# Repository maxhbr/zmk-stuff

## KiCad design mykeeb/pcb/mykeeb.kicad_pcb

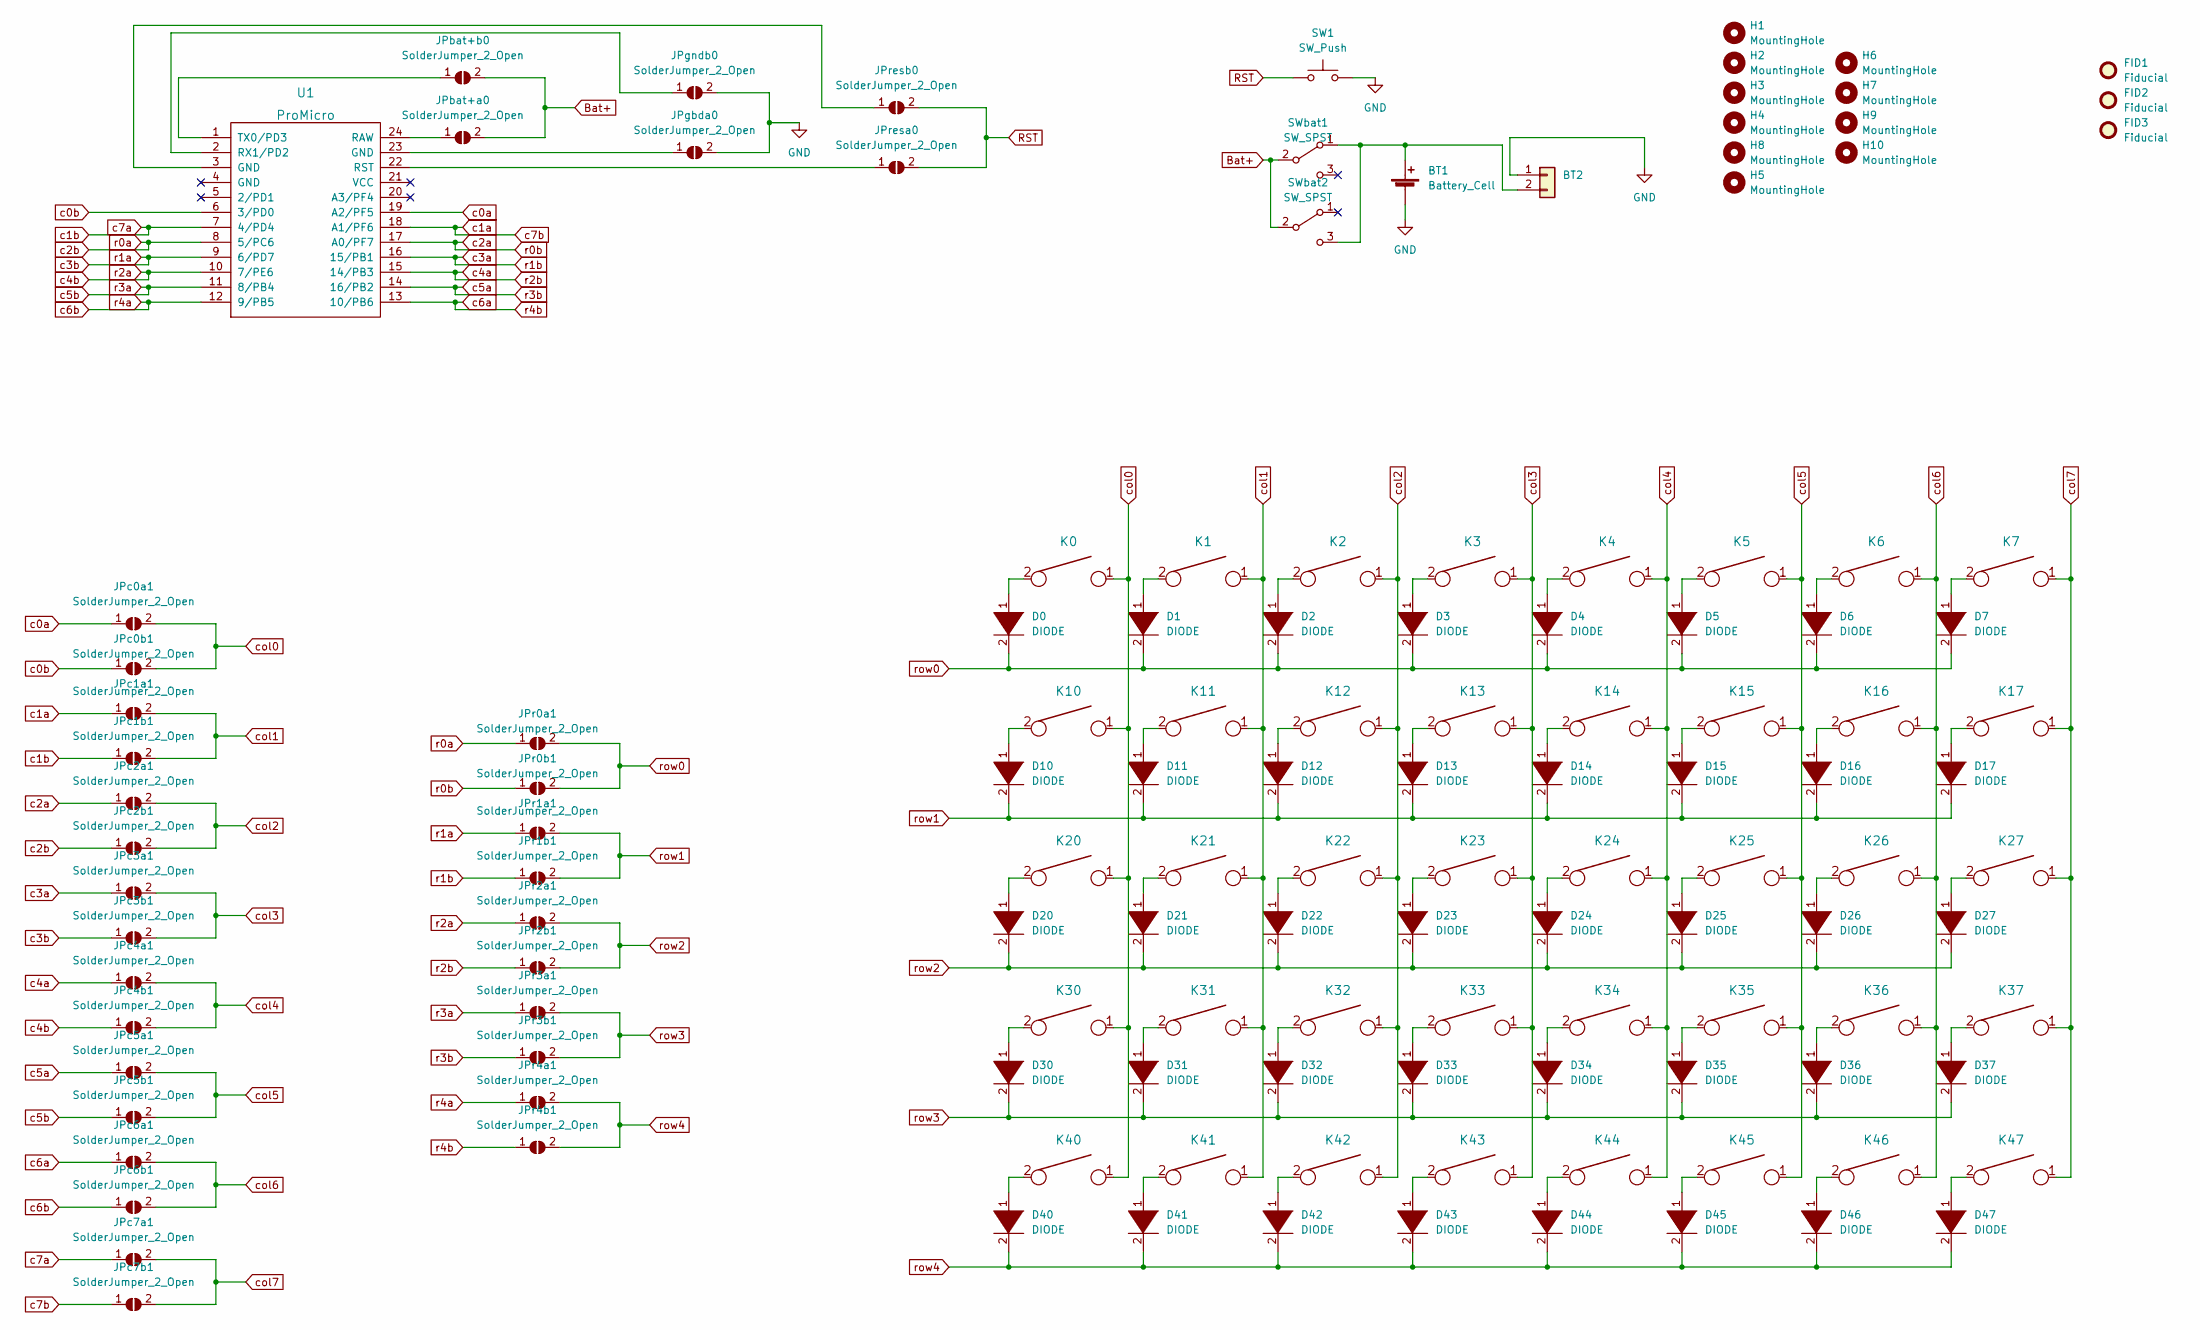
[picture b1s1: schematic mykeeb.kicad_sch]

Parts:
BT1: Battery_Cell; JST_PH_S2B-PH-K_1x02_P2.00mm_Horizontal
BT2: (no value)
D0, D1, D2, D3, D4, D5, D6, D7, D10, D11, D12, D13, D14, D15, D16, D17, D20, D21, D22, D23, D24, D25, D26, D27, D30, D31, D32, D33, D34, D35, D36, D37, D40, D41, D42, D43, D44, D45, D46, D47: DIODE; D_SOD123F
FID1, FID2, FID3: Fiducial; Fiducial_1mm_Mask2mm
H1, H2, H3, H4, H5, H8: MountingHole; MountingHole_3.2mm_M3
H6, H7, H9, H10: MountingHole; MountingHole_2.2mm_M2
JPbat+a0: SolderJumper_2_Open; SolderJumper-2_P1.3mm_Open_TrianglePad1.0x1.5mm
JPbat+b0: SolderJumper_2_Open; SolderJumper-2_P1.3mm_Open_TrianglePad1.0x1.5mm
JPc0a1, JPc0b1, JPc1a1, JPc1b1, JPc2a1, JPc2b1, JPc3a1, JPc3b1, JPc4a1, JPc4b1, JPc5a1, JPc5b1, JPc6a1, JPc6b1, JPc7a1, JPc7b1: SolderJumper_2_Open; SolderJumper-2_P1.3mm_Open_TrianglePad1.0x1.5mm
JPgbda0: SolderJumper_2_Open; SolderJumper-2_P1.3mm_Open_TrianglePad1.0x1.5mm
JPgndb0: SolderJumper_2_Open; SolderJumper-2_P1.3mm_Open_TrianglePad1.0x1.5mm
JPr0a1, JPr0b1, JPr1a1, JPr1b1, JPr2a1, JPr2b1, JPr3a1, JPr3b1, JPr4a1, JPr4b1: SolderJumper_2_Open; SolderJumper-2_P1.3mm_Open_TrianglePad1.0x1.5mm
JPresa0: SolderJumper_2_Open; SolderJumper-2_P1.3mm_Open_TrianglePad1.0x1.5mm
JPresb0: SolderJumper_2_Open; SolderJumper-2_P1.3mm_Open_TrianglePad1.0x1.5mm
K0, K1, K2, K3, K4, K5, K7, K10, K11, K12, K13, K14, K15, K20, K21, K22, K23, K24, K25, K30, K31, K32, K33, K34, K35, K36, K40, K41, K42, K43, K44: KEYSW; Kailh_socket_MX_optional_reversible_1u
K6, K16, K45: KEYSW; Kailh_socket_MX_optional_reversible_1.25u
K17, K27, K37, K47: KEYSW; SW_PUSH_6mm_H8mm
K26, K46: KEYSW; Kailh_socket_MX_optional_reversible_1.5u
SW1: SW_Push; SW_PUSH_6mm
SWbat1, SWbat2: SW_SPST; SW_SPDT_PCM12
U1: ProMicro; ArduinoProMicro-BackSide

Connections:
Bat+: JPbat+a0.2 (B), JPbat+b0.2 (B), SWbat1.2 (B), SWbat2.2 (B)
GND: BT1.2 (-), BT2.1, JPgbda0.2 (B), JPgndb0.2 (B), SW1.2
unnamed: BT1.1 (+), BT2.2, SWbat1.1 (A), SWbat2.3 (C)
unnamed: D0.1 (K), K0.2
unnamed: D1.1 (K), K1.2
unnamed: D2.1 (K), K2.2
unnamed: D3.1 (K), K3.2
unnamed: D4.1 (K), K4.2
unnamed: D5.1 (K), K5.2
unnamed: D6.1 (K), K6.2
unnamed: D7.1 (K), K7.2
unnamed: D10.1 (K), K10.2
unnamed: D11.1 (K), K11.2
unnamed: D12.1 (K), K12.2
unnamed: D13.1 (K), K13.2
unnamed: D14.1 (K), K14.2
unnamed: D15.1 (K), K15.2
unnamed: D16.1 (K), K16.2
unnamed: D17.1 (K), K17.2
unnamed: D20.1 (K), K20.2
unnamed: D21.1 (K), K21.2
unnamed: D22.1 (K), K22.2
unnamed: D23.1 (K), K23.2
unnamed: D24.1 (K), K24.2
unnamed: D25.1 (K), K25.2
unnamed: D26.1 (K), K26.2
unnamed: D27.1 (K), K27.2
unnamed: D30.1 (K), K30.2
unnamed: D31.1 (K), K31.2
unnamed: D32.1 (K), K32.2
unnamed: D33.1 (K), K33.2
unnamed: D34.1 (K), K34.2
unnamed: D35.1 (K), K35.2
unnamed: D36.1 (K), K36.2
unnamed: D37.1 (K), K37.2
unnamed: D40.1 (K), K40.2
unnamed 36: D41.1 (K), K41.2; also elsewhere on the board
unnamed 37: D42.1 (K), K42.2; also elsewhere on the board
unnamed 38: D43.1 (K), K43.2; also elsewhere on the board
unnamed: D44.1 (K), K44.2
unnamed: D45.1 (K), K45.2
unnamed: D46.1 (K), K46.2
unnamed: D47.1 (K), K47.2
unnamed: JPbat+a0.1 (A), U1.24 (RAW)
unnamed: JPbat+b0.1 (A), U1.1 (TX0/PD3)
unnamed: JPgbda0.1 (A), U1.23 (GND)
unnamed: JPgndb0.1 (A), U1.2 (RX1/PD2)
unnamed: JPresa0.1 (A), U1.22 (RST)
unnamed: JPresb0.1 (A), U1.3 (GND)
RST: JPresa0.2 (B), JPresb0.2 (B), SW1.1
c0a: JPc0a1.1 (A), U1.19 (A2/PF5)
c0b: JPc0b1.1 (A), U1.6 (3/PD0)
c1a: JPc1a1.1 (A), JPc7b1.1 (A), U1.18 (A1/PF6)
c1b: JPc1b1.1 (A), JPc7a1.1 (A), U1.7 (4/PD4)
c2a: JPc2a1.1 (A), JPr0b1.1 (A), U1.17 (A0/PF7)
c2b: JPc2b1.1 (A), JPr0a1.1 (A), U1.8 (5/PC6)
c3a: JPc3a1.1 (A), JPr1b1.1 (A), U1.16 (15/PB1)
c3b: JPc3b1.1 (A), JPr1a1.1 (A), U1.9 (6/PD7)
c4a: JPc4a1.1 (A), JPr2b1.1 (A), U1.15 (14/PB3)
c4b: JPc4b1.1 (A), JPr2a1.1 (A), U1.10 (7/PE6)
c5a: JPc5a1.1 (A), JPr3b1.1 (A), U1.14 (16/PB2)
c5b: JPc5b1.1 (A), JPr3a1.1 (A), U1.11 (8/PB4)
c6a: JPc6a1.1 (A), JPr4b1.1 (A), U1.13 (10/PB6)
c6b: JPc6b1.1 (A), JPr4a1.1 (A), U1.12 (9/PB5)
col0: JPc0a1.2 (B), JPc0b1.2 (B), K0.1, K10.1, K20.1, K30.1, K40.1
col1: JPc1a1.2 (B), JPc1b1.2 (B), K1.1, K11.1, K21.1, K31.1, K41.1; also elsewhere on the board
col2: JPc2a1.2 (B), JPc2b1.2 (B), K2.1, K12.1, K22.1, K32.1, K42.1; also elsewhere on the board
col3: JPc3a1.2 (B), JPc3b1.2 (B), K3.1, K13.1, K23.1, K33.1, K43.1; also elsewhere on the board
col4: JPc4a1.2 (B), JPc4b1.2 (B), K4.1, K14.1, K24.1, K34.1, K44.1
col5: JPc5a1.2 (B), JPc5b1.2 (B), K5.1, K15.1, K25.1, K35.1, K45.1
col6: JPc6a1.2 (B), JPc6b1.2 (B), K6.1, K16.1, K26.1, K36.1, K46.1
col7: JPc7a1.2 (B), JPc7b1.2 (B), K7.1, K17.1, K27.1, K37.1, K47.1
row0: D0.2 (A), D1.2 (A), D2.2 (A), D3.2 (A), D4.2 (A), D5.2 (A), D6.2 (A), D7.2 (A), JPr0a1.2 (B), JPr0b1.2 (B)
row1: D10.2 (A), D11.2 (A), D12.2 (A), D13.2 (A), D14.2 (A), D15.2 (A), D16.2 (A), D17.2 (A), JPr1a1.2 (B), JPr1b1.2 (B)
row2: D20.2 (A), D21.2 (A), D22.2 (A), D23.2 (A), D24.2 (A), D25.2 (A), D26.2 (A), D27.2 (A), JPr2a1.2 (B), JPr2b1.2 (B)
row3: D30.2 (A), D31.2 (A), D32.2 (A), D33.2 (A), D34.2 (A), D35.2 (A), D36.2 (A), D37.2 (A), JPr3a1.2 (B), JPr3b1.2 (B)
row4: D40.2 (A), D41.2 (A), D42.2 (A), D43.2 (A), D44.2 (A), D45.2 (A), D46.2 (A), D47.2 (A), JPr4a1.2 (B), JPr4b1.2 (B)

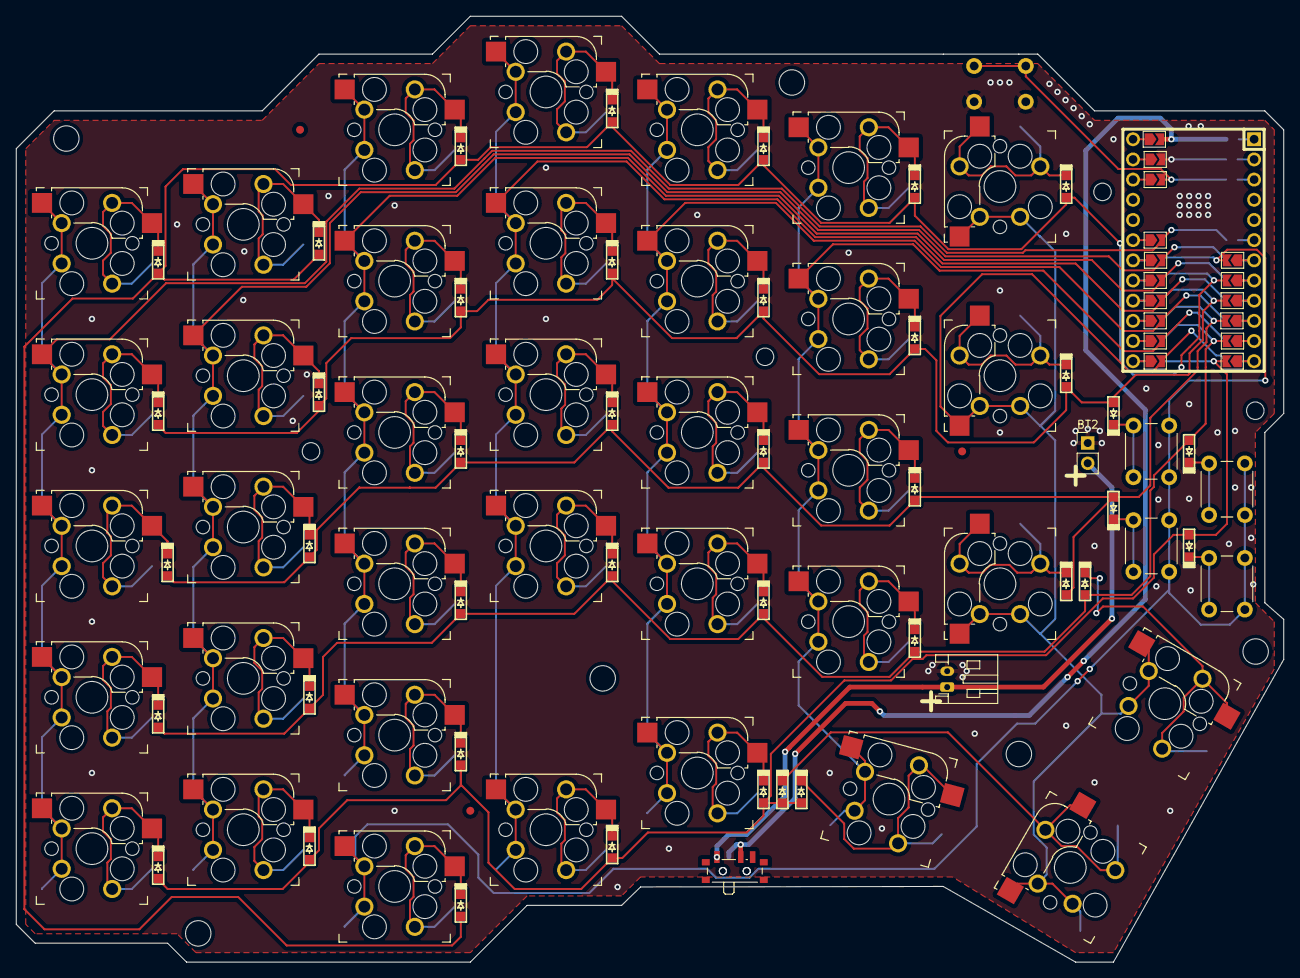
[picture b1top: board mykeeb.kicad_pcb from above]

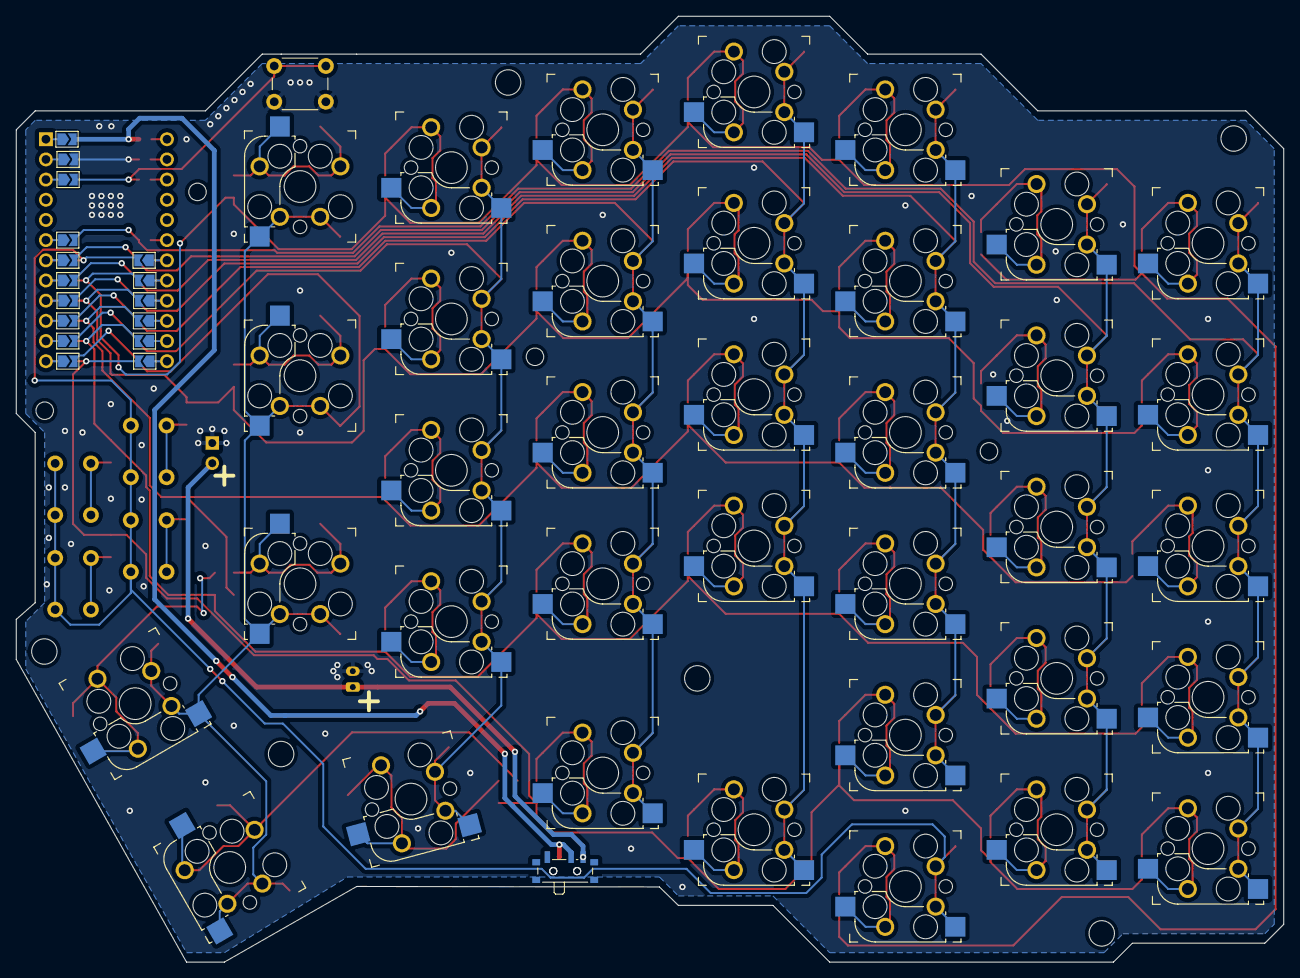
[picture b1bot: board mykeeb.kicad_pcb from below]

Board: 2 copper layers, 159.5 x 119.1 mm, 131 parts (19 on the bottom side), 77 nets.

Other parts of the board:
locked: KEYSW; Kailh_socket_MX_optional_reversible_1u
locked#2, locked#3: KEYSW; Kailh_socket_MX_optional_reversible_1u
locked#4: MountingHole; MountingHole_3.2mm_M3

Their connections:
unnamed 36: locked.2; also elsewhere on the board
unnamed 37: locked#2.2; also elsewhere on the board
unnamed 38: locked#3.2; also elsewhere on the board
col1: locked.1; also elsewhere on the board
col2: locked#2.1; also elsewhere on the board
col3: locked#3.1; also elsewhere on the board

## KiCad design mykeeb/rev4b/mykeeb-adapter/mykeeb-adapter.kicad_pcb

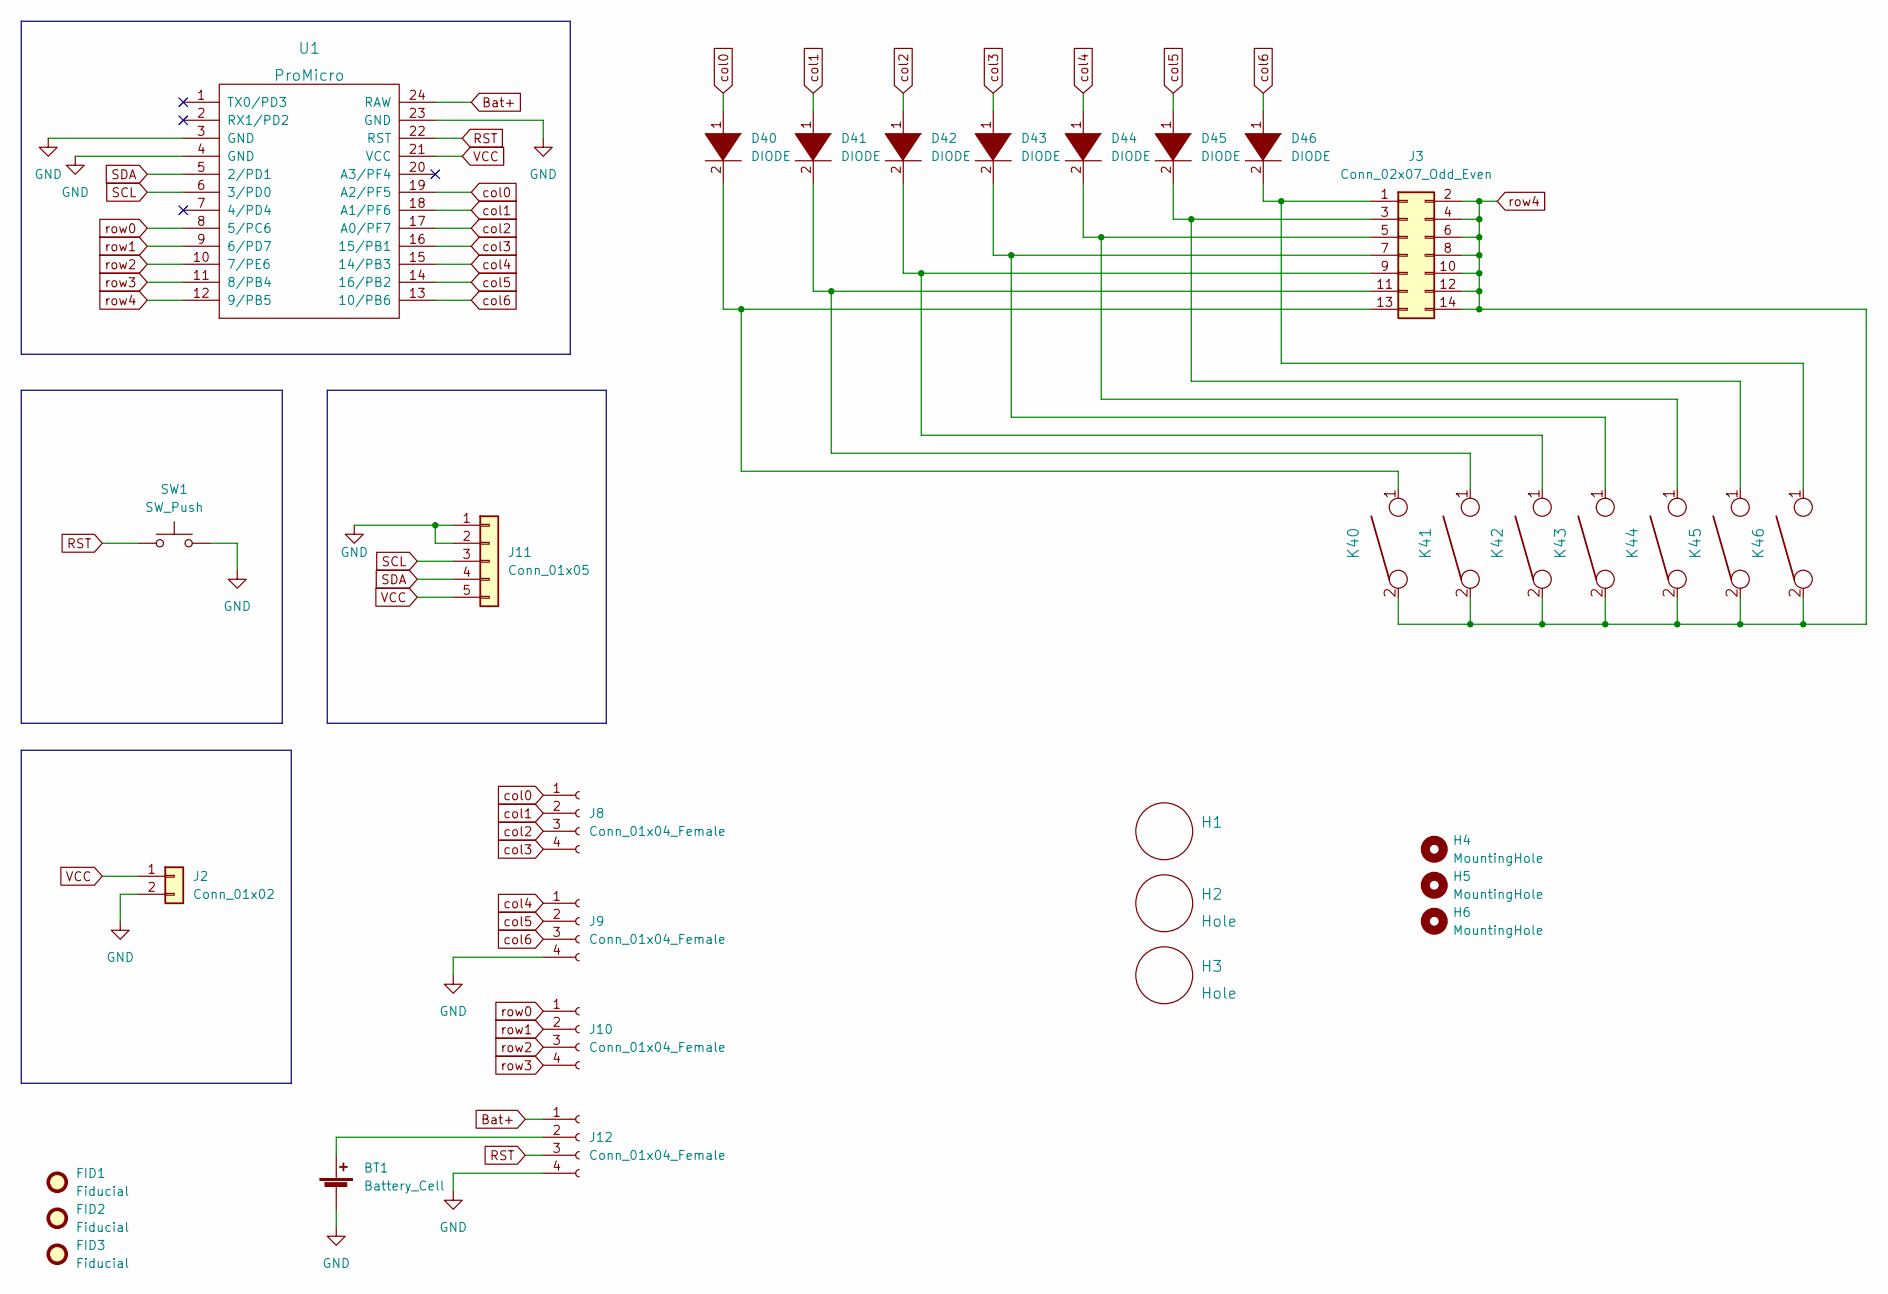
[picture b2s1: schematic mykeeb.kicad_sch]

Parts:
BT1: Battery_Cell; JST_PH_S2B-PH-K_1x02_P2.00mm_Horizontal
D40, D41, D42, D43, D44, D45, D46: DIODE; my_dual_D_SOD123F_v2b
FID1, FID2, FID3: Fiducial; Fiducial_1mm_Mask2mm
H1: (no value)
H2, H3: Hole; breakaway
H4, H5, H6: MountingHole; MountingHole_3.2mm_M3
J2: Conn_01x02; PinHeader_1x02_P2.54mm_Vertical
J3: Conn_02x07_Odd_Even; PinHeader_2x07_P2.54mm_Vertical
J8, J9, J10, J12: Conn_01x04_Female; PinSocket_1x04_P2.54mm_Vertical
J11: Conn_01x05; PinSocket_1x05_P2.54mm_Vertical
K40, K41, K43, K44, K45, K46: KEYSW; Kailh_socket_MX_reversible_1u
K42: KEYSW; Kailh_socket_MX_reversible_1.25u
SW1: SW_Push; SW_PUSH_6mm
U1: ProMicro; my_reversible_Pro_Micro

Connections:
Bat+: J12.1, U1.24 (RAW)
GND: BT1.2 (-), J2.2, J9.4, J11.1, J11.2, J12.4, SW1.2, U1.3 (GND), U1.4 (GND), U1.23 (GND)
unnamed: BT1.1 (+), J12.2
unnamed: D40.2 (A), J3.13, K40.1
unnamed: D41.2 (A), J3.11, K41.1
unnamed: D42.2 (A), J3.9, K42.1
unnamed: D43.2 (A), J3.7, K43.1
unnamed: D44.2 (A), J3.5, K44.1
unnamed: D45.2 (A), J3.3, K45.1
unnamed: D46.2 (A), J3.1, K46.1
RST: J12.3, SW1.1, U1.22 (RST)
SCL: J11.3, U1.6 (3/PD0)
SDA: J11.4, U1.5 (2/PD1)
VCC: J2.1, J11.5, U1.21 (VCC)
col0: D40.1 (K), J8.1, U1.19 (A2/PF5)
col1: D41.1 (K), J8.2, U1.18 (A1/PF6)
col2: D42.1 (K), J8.3, U1.17 (A0/PF7)
col3: D43.1 (K), J8.4, U1.16 (15/PB1)
col4: D44.1 (K), J9.1, U1.15 (14/PB3)
col5: D45.1 (K), J9.2, U1.14 (16/PB2)
col6: D46.1 (K), J9.3, U1.13 (10/PB6)
row0: J10.1, U1.8 (5/PC6)
row1: J10.2, U1.9 (6/PD7)
row2: J10.3, U1.10 (7/PE6)
row3: J10.4, U1.11 (8/PB4)
row4: J3.2, J3.4, J3.6, J3.8, J3.10, J3.12, J3.14, K40.2, K41.2, K42.2, K43.2, K44.2, K45.2, K46.2, U1.12 (9/PB5)

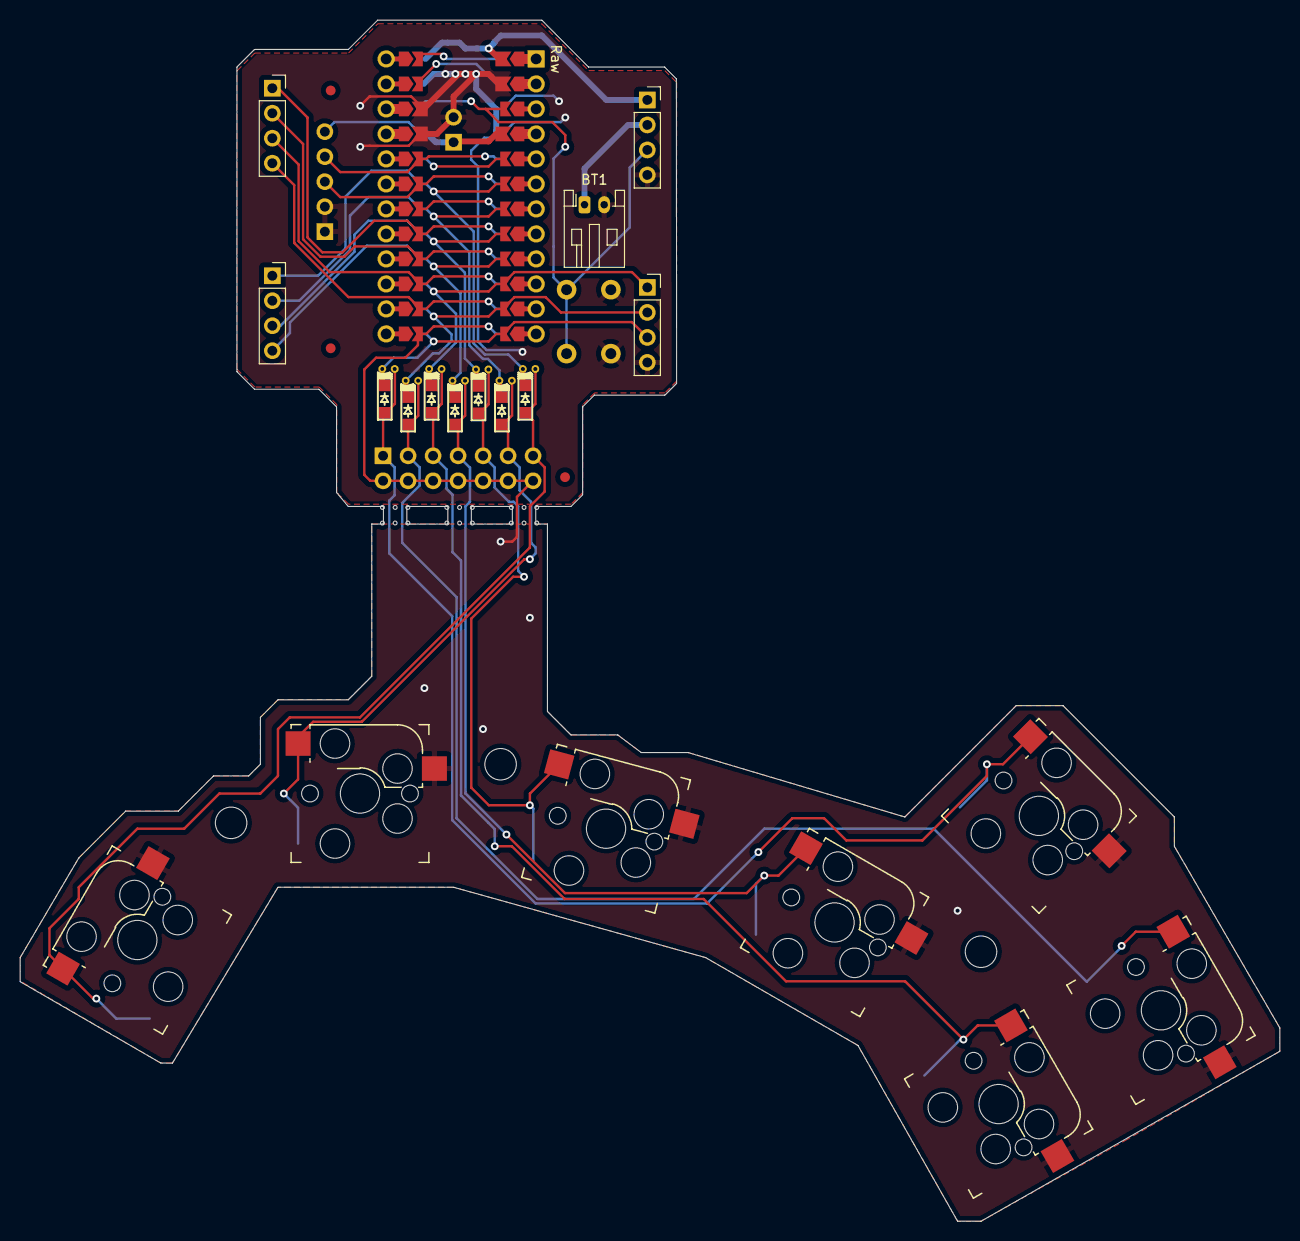
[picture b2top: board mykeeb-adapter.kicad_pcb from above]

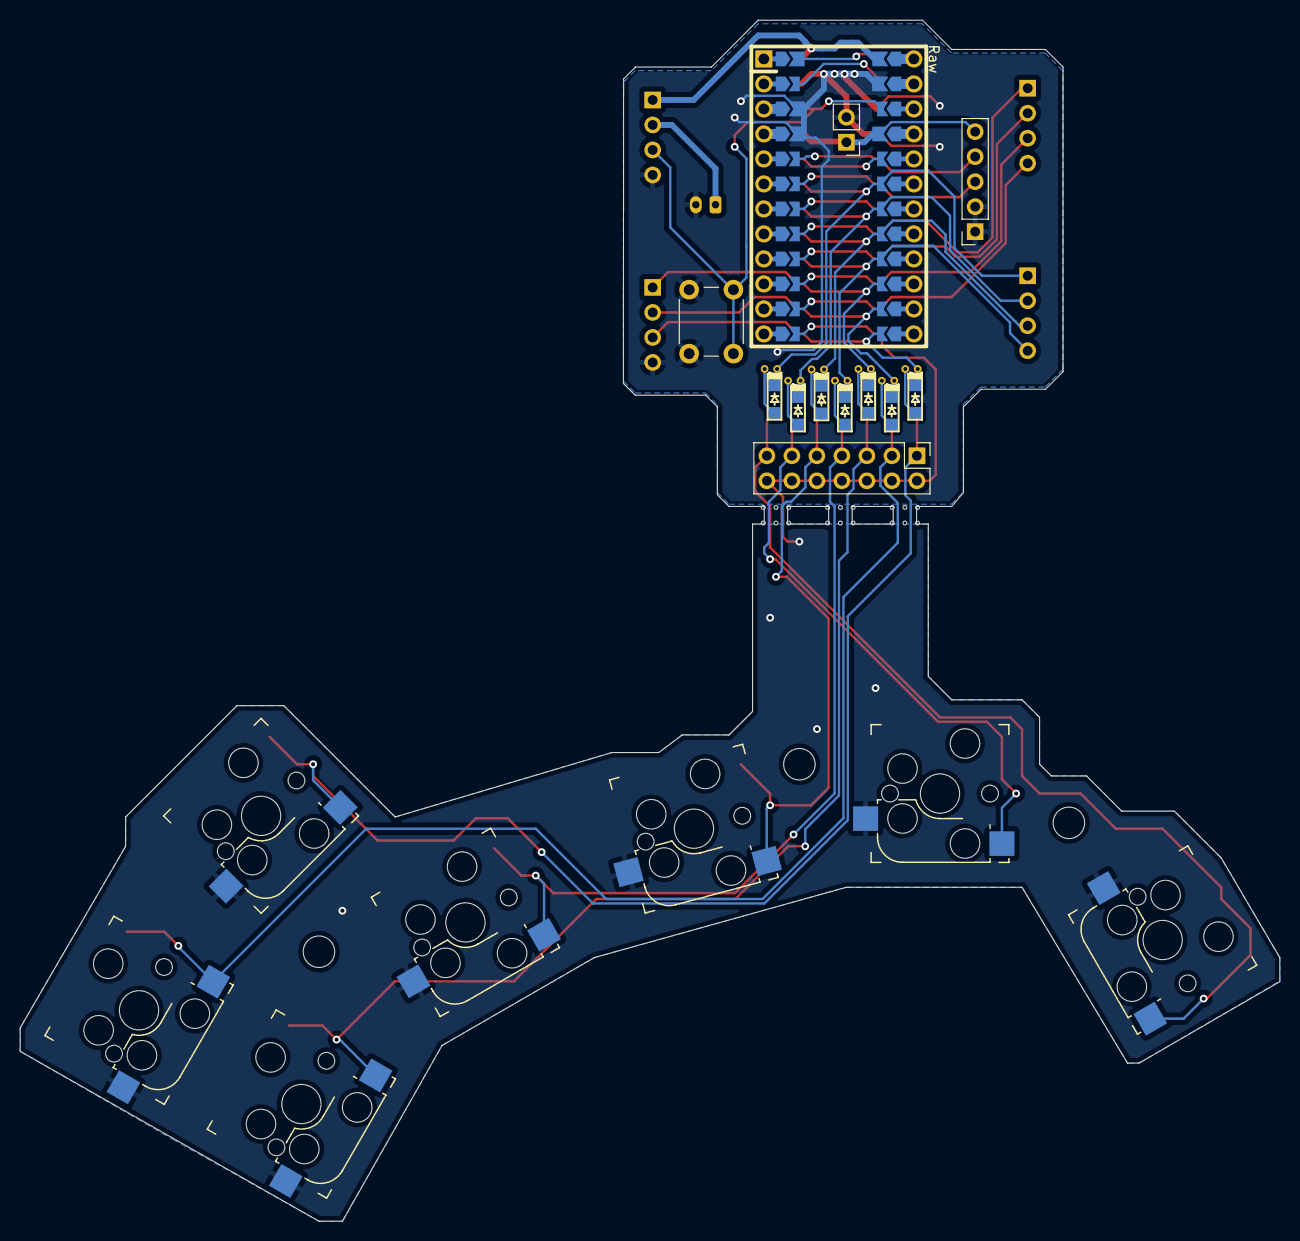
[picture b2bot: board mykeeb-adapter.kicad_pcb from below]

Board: 2 copper layers, 128.0 x 122.0 mm, 33 parts (5 on the bottom side), 26 nets.
